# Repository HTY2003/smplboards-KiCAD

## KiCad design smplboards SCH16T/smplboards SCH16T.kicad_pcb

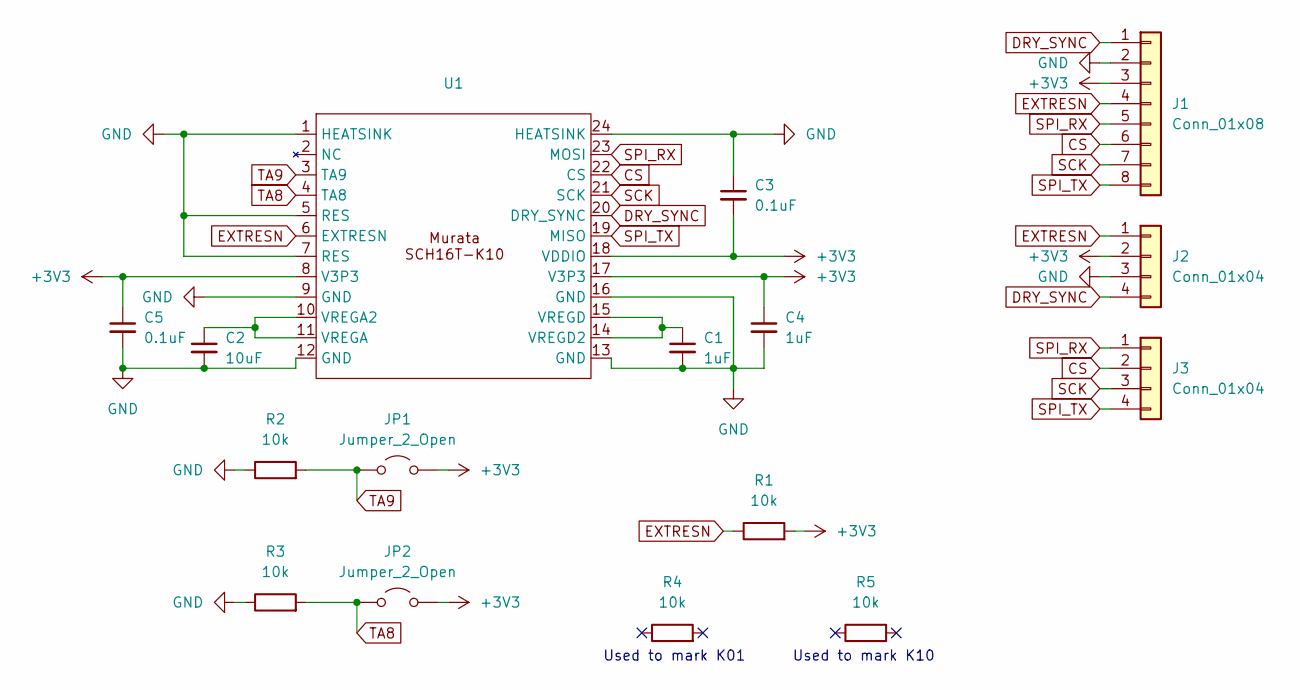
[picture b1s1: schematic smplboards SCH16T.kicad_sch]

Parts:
C1, C4: 1uF; C_0603_1608Metric
C2: 10uF; C_0805_2012Metric
C3, C5: 0.1uF; C_0402_1005Metric
J1: Conn_01x08; JST_SH_SM08B-SRSS-TB_1x08-1MP_P1.00mm_Horizontal
J2, J3: Conn_01x04; PinSocket_1x04_P2.54mm_Vertical
JP1, JP2: Jumper_2_Open; SolderJumper-2_P1.3mm_Open_RoundedPad1.0x1.5mm
R1, R2, R3, R4, R5: 10k; R_0402_1005Metric
U1: SCH16T

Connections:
+3V3: C3.2, C4.1, C5.1, J1.3, J2.2, JP1.2 (B), JP2.2 (B), R1.2, U1.8 (V3P3), U1.17 (V3P3), U1.18 (VDDIO)
CS: J1.6, J3.2, U1.22 (CS)
DRY_SYNC: J1.1, J2.4, U1.20 (DRY_SYNC)
EXTRESN: J1.4, J2.1, R1.1, U1.6 (EXTRESN)
GND: C1.2, C2.2, C3.1, C4.2, C5.2, J1.2, J2.3, R2.1, R3.1, U1.1 (HEATSINK), U1.5 (RES), U1.7 (RES), U1.9 (GND), U1.12 (GND), U1.13 (GND), U1.16 (GND), U1.24 (HEATSINK)
unnamed: C2.1, U1.10 (VREGA2), U1.11 (VREGA)
unnamed: C1.1, U1.14 (VREGD2), U1.15 (VREGD)
SCK: J1.7, J3.3, U1.21 (SCK)
SPI_RX: J1.5, J3.1, U1.23 (MOSI)
SPI_TX: J1.8, J3.4, U1.19 (MISO)
TA8: JP2.1 (A), R3.2, U1.4 (TA8)
TA9: JP1.1 (A), R2.2, U1.3 (TA9)

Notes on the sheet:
Used to mark K10
Used to mark K01

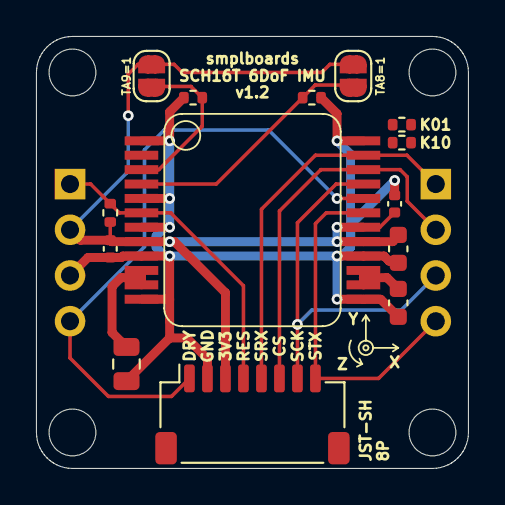
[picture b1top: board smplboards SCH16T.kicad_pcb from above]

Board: 2 copper layers, 24.0 x 24.0 mm, 16 parts (0 on the bottom side), 12 nets.

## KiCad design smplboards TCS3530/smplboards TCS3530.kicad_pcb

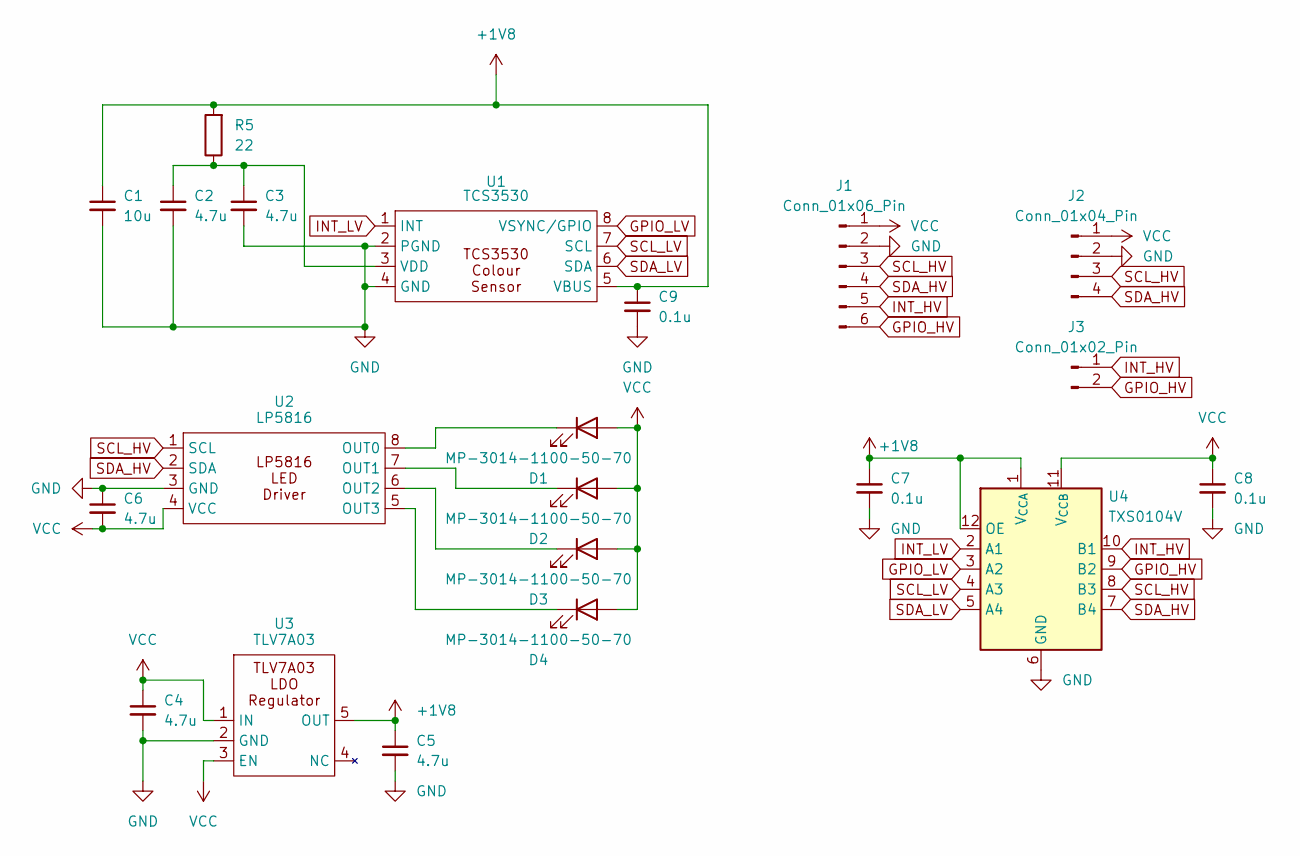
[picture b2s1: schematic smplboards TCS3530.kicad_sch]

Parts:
C1: 10u; C_0603_1608Metric
C2, C3, C4, C5, C6: 4.7u; C_0402_1005Metric
C7, C8, C9: 0.1u; C_0402_1005Metric
D1, D2, D3, D4: MP-3014-1100-50-70; LED_MP-3014-1100-50-80
J1: Conn_01x06_Pin; JST_SH_SM06B-SRSS-TB_1x06-1MP_P1.00mm_Horizontal
J2: Conn_01x04_Pin; PinHeader_1x04_P2.54mm_Vertical
J3: Conn_01x02_Pin; PinHeader_1x02_P2.54mm_Vertical
R5: 22; R_0402_1005Metric
U1: TCS3530; Sensor_Colour_TCS3530
U2: LP5816; SOT-583-8
U3: TLV7A03; SOT-23-5
U4: TXS0104V; Texas_R-PUQFN-N12

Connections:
+1V8: C1.1, C5.1, C7.1, C9.1, R5.2, U1.5 (VBUS), U3.5 (OUT), U4.1 (V_{CCA}), U4.12 (OE)
GND: C1.2, C2.2, C3.2, C4.2, C5.2, C6.1, C7.2, C8.2, C9.2, J1.2, J2.2, U1.2 (PGND), U1.4 (GND), U2.3 (GND), U3.2 (GND), U4.6 (GND)
GPIO_HV: J1.6, J3.2, U4.9 (B2)
GPIO_LV: U1.8 (VSYNC/GPIO), U4.3 (A2)
INT_HV: J1.5, J3.1, U4.10 (B1)
INT_LV: U1.1 (INT), U4.2 (A1)
unnamed: D1.1 (K), U2.8 (OUT0)
unnamed: D2.1 (K), U2.7 (OUT1)
unnamed: D3.1 (K), U2.6 (OUT2)
unnamed: D4.1 (K), U2.5 (OUT3)
unnamed: C2.1, C3.1, R5.1, U1.3 (VDD)
SCL_HV: J1.3, J2.3, U2.1 (SCL), U4.8 (B3)
SCL_LV: U1.7 (SCL), U4.4 (A3)
SDA_HV: J1.4, J2.4, U2.2 (SDA), U4.7 (B4)
SDA_LV: U1.6 (SDA), U4.5 (A4)
VCC: C4.1, C6.2, C8.1, D1.2 (A), D2.2 (A), D3.2 (A), D4.2 (A), J1.1, J2.1, U2.4 (VCC), U3.1 (IN), U3.3 (EN), U4.11 (V_{CCB})

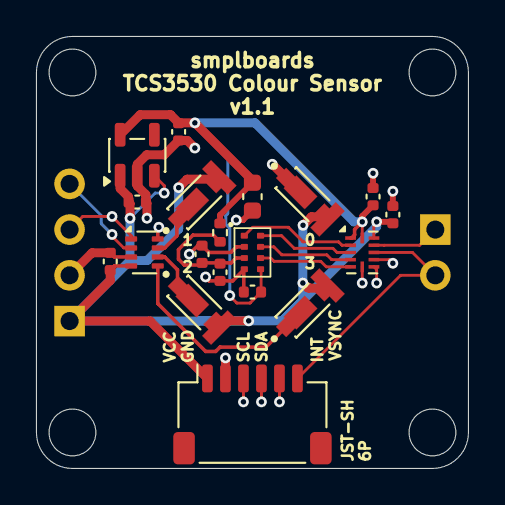
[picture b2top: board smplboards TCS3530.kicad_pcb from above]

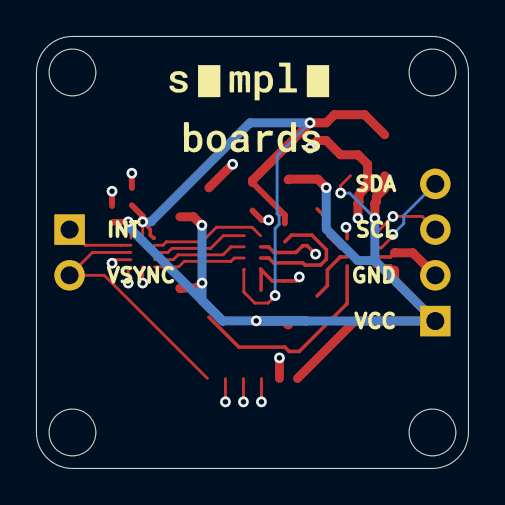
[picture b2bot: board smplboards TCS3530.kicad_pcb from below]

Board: 4 copper layers, 24.0 x 24.0 mm, 21 parts (2 on the bottom side), 16 nets.

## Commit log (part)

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2025-07-26 Add SCH16T design files
2026-05-02 Add TCS3530 v1.1
2026-05-02 Add SCH16T v1.2 (only a cosmetic update)
2026-05-02 Finalize TCS3530 v1.1
